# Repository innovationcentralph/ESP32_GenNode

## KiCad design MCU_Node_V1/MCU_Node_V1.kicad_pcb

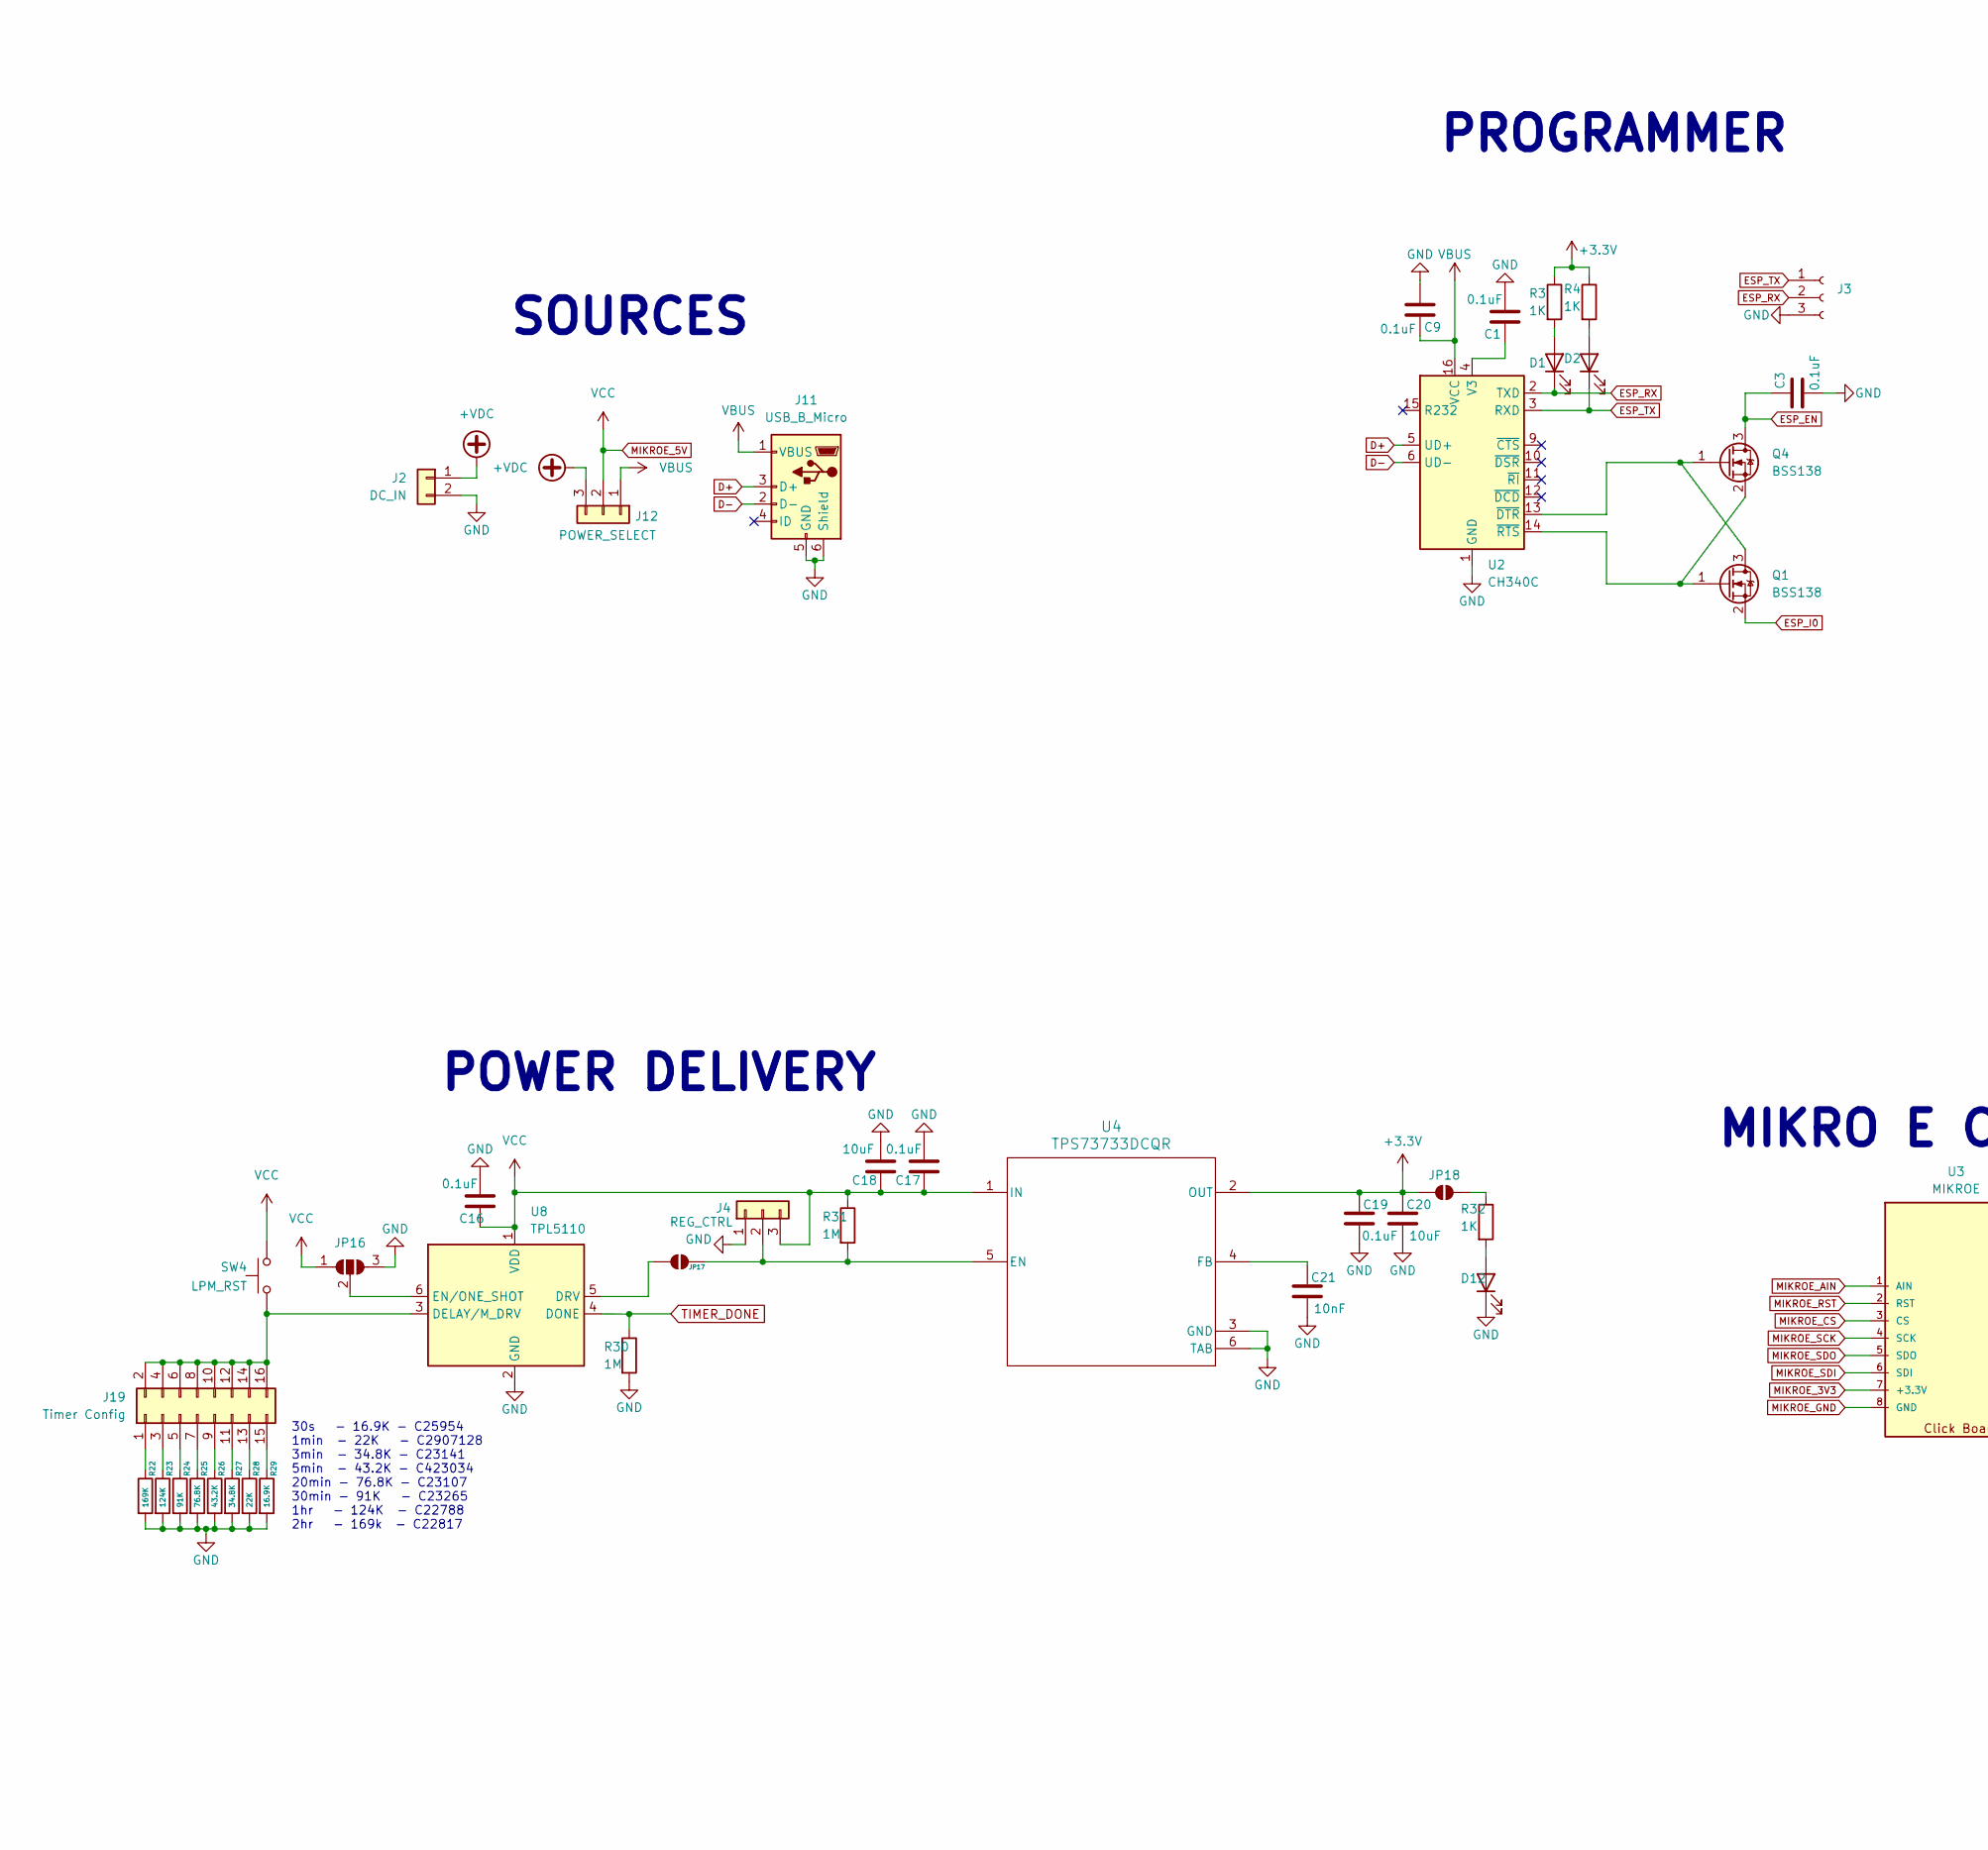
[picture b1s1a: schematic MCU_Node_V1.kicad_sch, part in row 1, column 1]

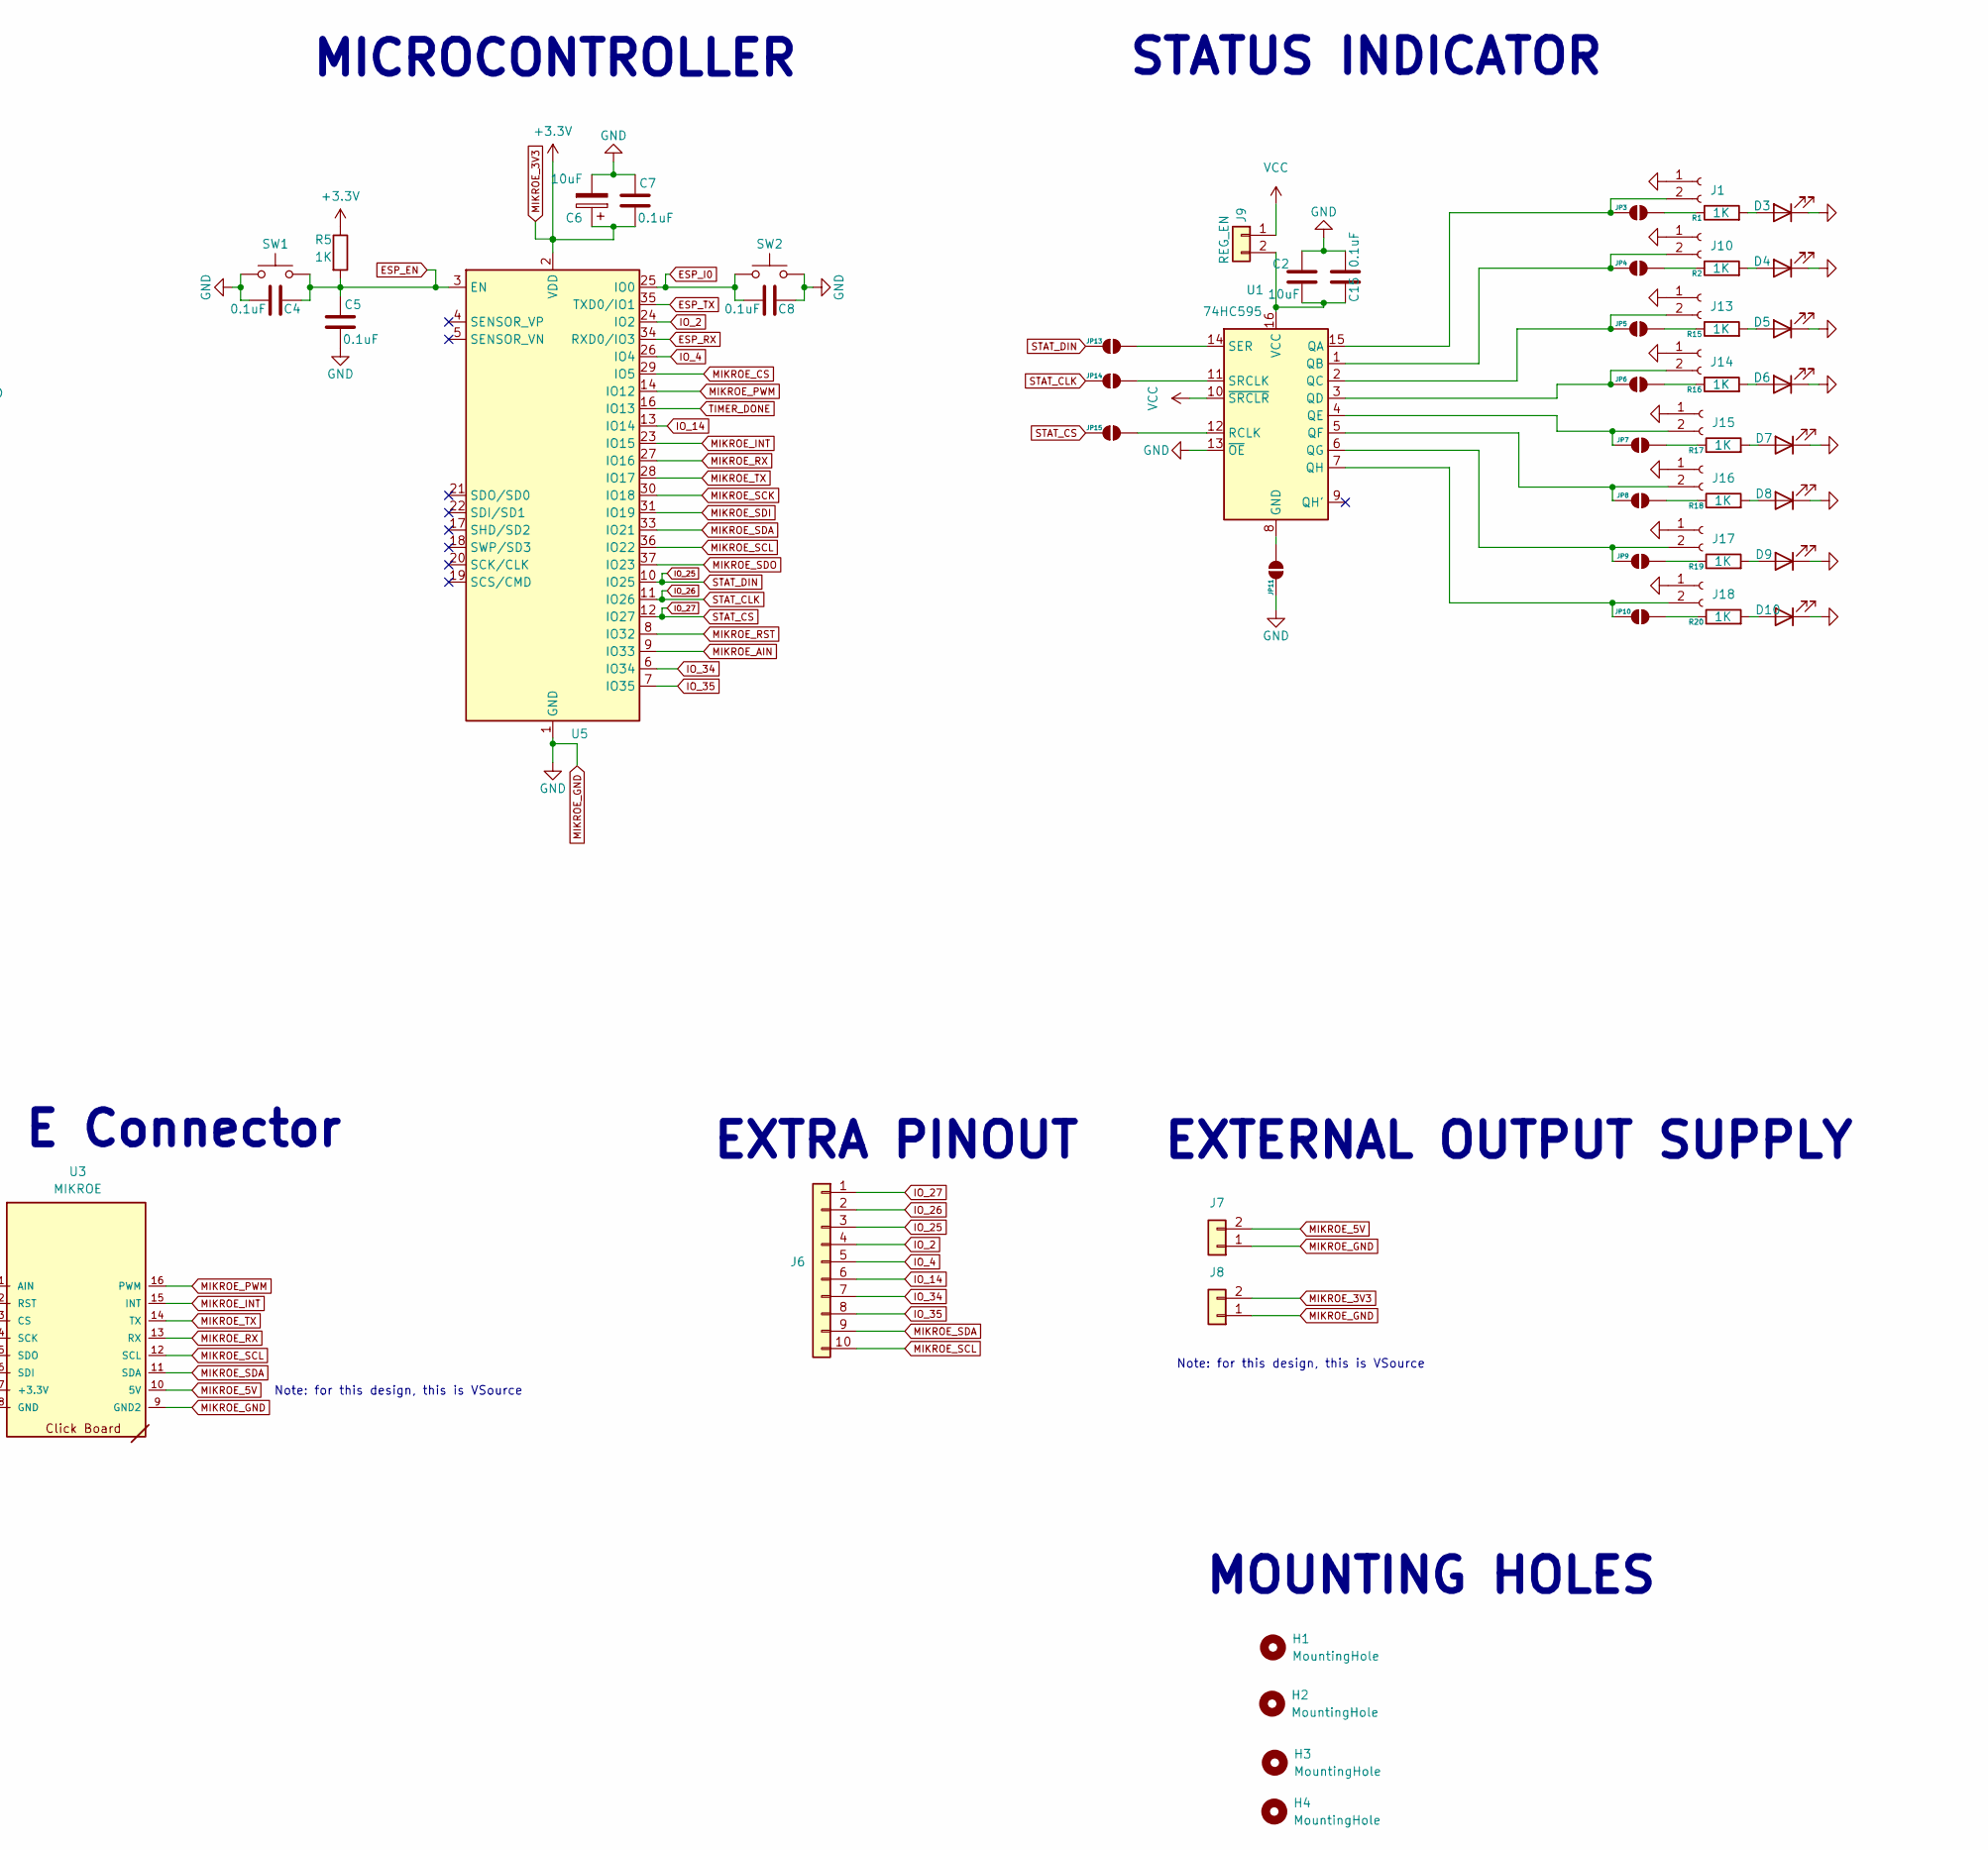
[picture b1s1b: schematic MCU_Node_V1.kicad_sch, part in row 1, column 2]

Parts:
C1, C3, C4, C5, C7, C8, C9, C15, C16, C17, C19: 0.1uF; C_0402_1005Metric; LCSC C60474
C2, C6, C18, C20: 10uF; C_0805_2012Metric_Pad1.18x1.45mm_HandSolder; LCSC C15850
C21: 10nF; C_0402_1005Metric; LCSC C60133
D1, D2, D3, D4, D5, D6, D7, D8, D9, D10, D12: LED; LED_0805_2012Metric_Pad1.15x1.40mm_HandSolder; LCSC C2297
H1, H2, H3, H4: MountingHole; MountingHole_3.2mm_M3_DIN965_Pad
J1, J10, J13, J14, J15, J16, J17, J18: Conn_01x02_Socket; PinHeader_1x02_P2.54mm_Vertical
J2: DC_IN; JST_EH_S2B-EH_1x02_P2.50mm_Horizontal
J3: Conn_01x03_Socket; PinHeader_1x03_P2.54mm_Vertical
J4: REG_CTRL; PinHeader_1x03_P2.54mm_Vertical
J6: Conn_01x10; PinHeader_1x10_P2.54mm_Vertical
J7, J8: Conn_01x02; PinHeader_1x02_P2.54mm_Vertical
J9: REG_EN; PinHeader_1x02_P2.54mm_Vertical
J11: USB_B_Micro; USB_Micro-B_Molex-105017-0001; LCSC C404969
J12: POWER_SELECT; PinHeader_1x03_P2.54mm_Vertical
J19: Timer Config; IDC-Header_2x08_P2.54mm_Vertical
JP3, JP4, JP5, JP6, JP7, JP8, JP9, JP10, JP11, JP13, JP14, JP15, JP17, JP18: SolderJumper_2_Open; SolderJumper-2_P1.3mm_Open_Pad1.0x1.5mm
JP16: SolderJumper_3_Open; SolderJumper-3_P1.3mm_Open_Pad1.0x1.5mm
Q1, Q4: BSS138; SOT-23; LCSC C426569
R1, R2, R3, R4, R5, R15, R16, R17, R18, R19, R20, R32: 1K; R_0603_1608Metric_Pad0.98x0.95mm_HandSolder; LCSC C21190
R22: 169K; R_0603_1608Metric_Pad0.98x0.95mm_HandSolder; LCSC C22817
R23: 124K; R_0603_1608Metric_Pad0.98x0.95mm_HandSolder; LCSC C22788
R24: 91K; R_0603_1608Metric_Pad0.98x0.95mm_HandSolder; LCSC C23265
R25: 76.8K; R_0603_1608Metric_Pad0.98x0.95mm_HandSolder; LCSC C23107
R26: 43.2K; R_0603_1608Metric_Pad0.98x0.95mm_HandSolder; LCSC C423034
R27: 34.8K; R_0603_1608Metric_Pad0.98x0.95mm_HandSolder; LCSC C23141
R28: 22K; R_0603_1608Metric_Pad0.98x0.95mm_HandSolder; LCSC C2907128
R29: 16.9K; R_0603_1608Metric_Pad0.98x0.95mm_HandSolder; LCSC C25954
R30, R31: 1M; R_0603_1608Metric_Pad0.98x0.95mm_HandSolder; LCSC C105578
SW1, SW2: SW_Push; SW_SPST_CK_RS282G05A3; LCSC C2689642
SW4: LPM_RST; SW_SPST_CK_RS282G05A3; LCSC C2689642
U1: 74HC595; SOIC-16_3.9x9.9mm_P1.27mm; LCSC C5947
U2: CH340C; SOIC-16_3.9x9.9mm_P1.27mm; LCSC C84681
U3: MIKROE; MIKROE-3800
U4: TPS73733DCQR; DCQ0006A; LCSC C31334
U5: ESP32-WROOM-32; LCSC C529577
U8: TPL5110; SOT-23-6; LCSC C1539984

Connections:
+VDC: J2.1, J12.3
D+: J11.3 (D+), U2.5 (UD+)
D-: J11.2 (D-), U2.6 (UD-)
ESP_EN: C3.2, C4.2, C5.2, Q4.3 (D), R5.2, SW1.2, U5.3 (EN)
ESP_I0: C8.1, Q1.2 (S), SW2.1, U5.25 (IO0)
ESP_RX: D1.1 (K), J3.2, U2.2 (TXD), U5.34 (RXD0/IO3)
ESP_TX: D2.1 (K), J3.1, U2.3 (RXD), U5.35 (TXD0/IO1)
IO_2: J6.4, U5.24 (IO2)
IO_4: J6.5, U5.26 (IO4)
IO_14: J6.6, U5.13 (IO14)
IO_25: J6.3, JP13.1 (A), U5.10 (IO25)
IO_26: J6.2, JP14.1 (A), U5.11 (IO26)
IO_27: J6.1, JP15.1 (A), U5.12 (IO27)
IO_34: J6.7, U5.6 (IO34)
IO_35: J6.8, U5.7 (IO35)
MIKROE_3V3: C6.1, C7.1, C19.2, C20.2, J8.2, JP18.1 (A), R3.1, R4.1, R5.1, U3.7 (+3.3V), U4.2 (OUT), U5.2 (VDD)
MIKROE_5V: C16.2, C17.2, C18.2, J4.3, J7.2, J9.1, J12.2, JP16.1 (A), R31.1, SW4.2, U1.10 (~SRCLR), U3.10 (5V), U4.1 (IN), U8.1 (VDD)
MIKROE_AIN: U3.1 (AIN), U5.9 (IO33)
MIKROE_CS: U3.3 (CS), U5.29 (IO5)
MIKROE_GND: C1.1, C2.1, C3.1, C4.1, C5.1, C6.2, C7.2, C8.2, C9.1, C15.1, C16.1, C17.1, C18.1, C19.1, C20.1, C21.1, D3.1 (K), D4.1 (K), D5.1 (K), D6.1 (K), D7.1 (K), D8.1 (K), D9.1 (K), D10.1 (K), D12.1 (K), J1.1, J2.2, J3.3, J4.1, J7.1, J8.1, J10.1, J11.5 (GND), J11.6 (Shield), J13.1, J14.1, J15.1, J16.1, J17.1, J18.1, JP11.1 (A), JP16.3 (B), R22.2, R23.2, R24.2, R25.2, R26.2, R27.2, R28.2, R29.2, R30.2, SW1.1, SW2.2, U1.13 (~OE), U2.1 (GND), U3.8 (GND), U3.9 (GND2), U4.3 (GND), U4.6 (TAB), U5.1 (GND), U5.15 (GND), U5.38 (GND), U5.39 (GND), U8.2 (GND)
MIKROE_INT: U3.15 (INT), U5.23 (IO15)
MIKROE_PWM: U3.16 (PWM), U5.14 (IO12)
MIKROE_RST: U3.2 (RST), U5.8 (IO32)
MIKROE_RX: U3.13 (RX), U5.27 (IO16)
MIKROE_SCK: U3.4 (SCK), U5.30 (IO18)
MIKROE_SCL: J6.10, U3.12 (SCL), U5.36 (IO22)
MIKROE_SDA: J6.9, U3.11 (SDA), U5.33 (IO21)
MIKROE_SDI: U3.6 (SDI), U5.31 (IO19)
MIKROE_SDO: U3.5 (SDO), U5.37 (IO23)
MIKROE_TX: U3.14 (TX), U5.28 (IO17)
unnamed: D1.2 (A), R3.2
unnamed: D2.2 (A), R4.2
unnamed: D3.2 (A), R1.2
unnamed: D4.2 (A), R2.2
unnamed: D5.2 (A), R15.2
unnamed: D6.2 (A), R16.2
unnamed: D7.2 (A), R17.2
unnamed: D8.2 (A), R18.2
unnamed: D9.2 (A), R19.2
unnamed: D10.2 (A), R20.2
unnamed: D12.2 (A), R32.2
unnamed: J1.2, JP3.1 (A), U1.15 (QA)
unnamed: J4.2, JP17.1 (A), R31.2, U4.5 (EN)
unnamed: C2.2, C15.2, J9.2, U1.16 (VCC)
unnamed: J10.2, JP4.1 (A), U1.1 (QB)
unnamed: J13.2, JP5.1 (A), U1.2 (QC)
unnamed: J14.2, JP6.1 (A), U1.3 (QD)
unnamed: J15.2, JP7.1 (A), U1.4 (QE)
unnamed: J16.2, JP8.1 (A), U1.5 (QF)
unnamed: J17.2, JP9.1 (A), U1.6 (QG)
unnamed: J18.2, JP10.1 (A), U1.7 (QH)
unnamed: J19.1, R22.1
unnamed: J19.3, R23.1
unnamed: J19.5, R24.1
unnamed: J19.7, R25.1
unnamed: J19.9, R26.1
unnamed: J19.2, J19.4, J19.6, J19.8, J19.10, J19.12, J19.14, J19.16, SW4.1, U8.3 (DELAY/M_DRV)
unnamed: J19.11, R27.1
unnamed: J19.13, R28.1
unnamed: J19.15, R29.1
unnamed: JP3.2 (B), R1.1
unnamed: JP4.2 (B), R2.1
unnamed: JP5.2 (B), R15.1
unnamed: JP6.2 (B), R16.1
unnamed: JP7.2 (B), R17.1
unnamed: JP8.2 (B), R18.1
unnamed: JP9.2 (B), R19.1
unnamed: JP10.2 (B), R20.1
unnamed: JP11.2 (B), U1.8 (GND)
unnamed: JP13.2 (B), U1.14 (SER)
unnamed: JP14.2 (B), U1.11 (SRCLK)
unnamed: JP15.2 (B), U1.12 (RCLK)
unnamed: JP16.2 (C), U8.6 (EN/ONE_SHOT)
unnamed: JP17.2 (B), U8.5 (DRV)
unnamed: JP18.2 (B), R32.1
unnamed: Q1.3 (D), Q4.1 (G), U2.13 (~DTR)
unnamed: Q1.1 (G), Q4.2 (S), U2.14 (~RTS)
unnamed: C1.2, U2.4 (V3)
unnamed: C21.2, U4.4 (FB)
TIMER_DONE: R30.1, U5.16 (IO13), U8.4 (DONE)
VBUS: C9.2, J11.1 (VBUS), J12.1, U2.16 (VCC)

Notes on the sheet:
MICROCONTROLLER
Note: for this design, this is VSource
PROGRAMMER
POWER DELIVERY
STATUS INDICATOR
MIKRO E Connector
SOURCES
MOUNTING HOLES
EXTRA PINOUT
EXTERNAL OUTPUT SUPPLY
30s - 16.9K - C25954 1min - 22K - C2907128 3min - 34.8K - C23141 5min - 43.2K - C423034 20min - 76.8K - C23107 30min - 91K - C23265 1hr - 124K - C22788 2hr - 169k - C22817

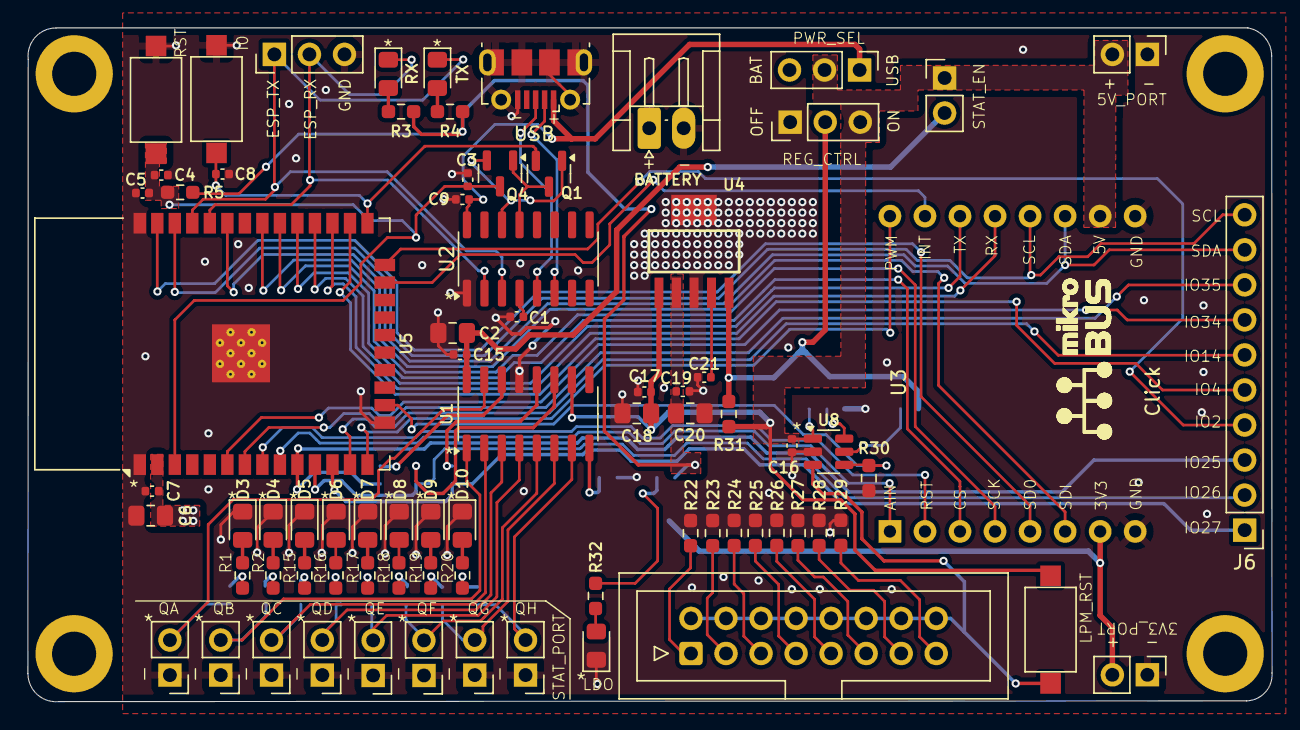
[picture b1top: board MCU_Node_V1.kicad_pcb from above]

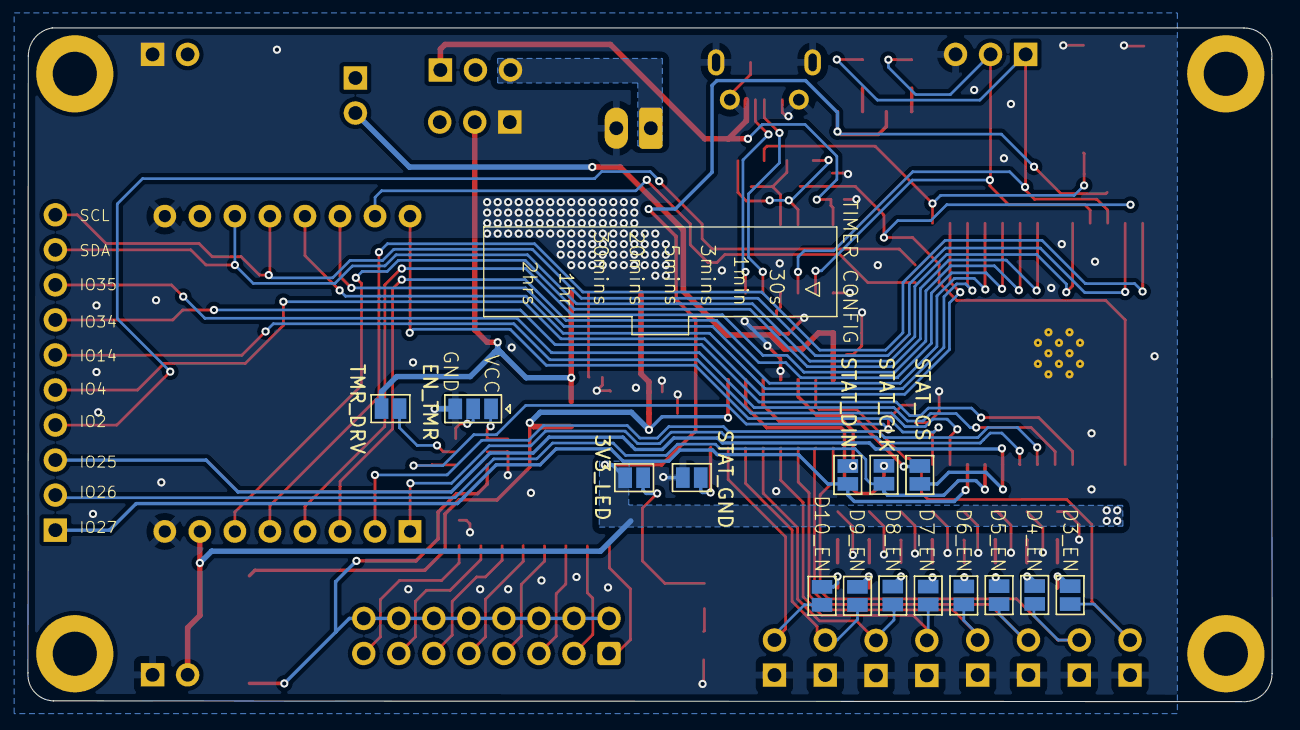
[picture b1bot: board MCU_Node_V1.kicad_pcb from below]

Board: 2 copper layers, 90.2 x 48.8 mm, 97 parts (15 on the bottom side), 81 nets.

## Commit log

2024-09-20 Initial Commit
    Done Schematic
2024-09-21 edit
    edited mikroe symbol & footprint
    edited extra pinouts
    added solder jumper 74HC595
    added mounting hole
2024-09-21 Updated 3.3V Regulator
    Used TPS73733 instead of AMS1117
    Added External Library Files for TPS37333
2024-09-21 Update Saved Files for 3V3 Regulator change
2024-09-22 -
    pcb - 60 percent
2024-09-22 -
    routing & placement done
2024-09-23 98 percent
    -drc warning negliglble
    -additional designation thru silkscreen for the timer and led ports
2024-09-24 done
    -to be approve
2024-10-12 panelize
    panelization on production folder
2024-10-14 -
    panelization drc checked , unconnected fix
